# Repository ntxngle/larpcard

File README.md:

# larpcard
what if we larped in larpzhen

It's a NFC that opens apple wallet or payment manager and, when recieving power from NFC communication, blinks the coin's LEDs sequentially.

|Id |Designator                   |Footprint|Quantity                                     |Designation   |Supplier and ref|FIELD7|FIELD8|
|---|-----------------------------|---------|---------------------------------------------|--------------|----------------|------|------|
|1  |D2,D3,D1                     |LED_0603_1608Metric|3                                            |LED           |3x C5278868     |      |      |
|2  |L1                           |1356ant  |1                                            |L             |                |      |      |
|3  |C3,C2,C4                     |C_0603_1608Metric|3                                            |4.7uF         |3x C51933292    |      |      |
|4  |Q2,Q3,Q1                     |SOT-23   |3                                            |NPN           |3x C2936640     |      |      |
|5  |R3,R5,R1                     |R_0603_1608Metric|3                                            |100k          |3x C73806       |      |      |
|6  |R2,R4,R6                     |R_0603_1608Metric|3                                            |100           |3x C2906981     |      |      |
|7  |C6                           |C_0603_1608Metric|1                                            |2pF           |1x C5936367     |      |      |
|8  |C1                           |C_0603_1608Metric|1                                            |220nF         |1x C354388      |      |      |
|9  |U1                           |TSSOP-8_3x3mm_P0.65mm|1                                            |NT3H2111W0FTTJ|1x C7432767     |      |      |
|10 |C5                           |C_0603_1608Metric|1                                            |10uF          |2x C15402       |      |      |
|11 |R8,R7                        |R_0603_1608Metric|2                                            |0             |1x C2654859     |      |      |

Slack username: i10

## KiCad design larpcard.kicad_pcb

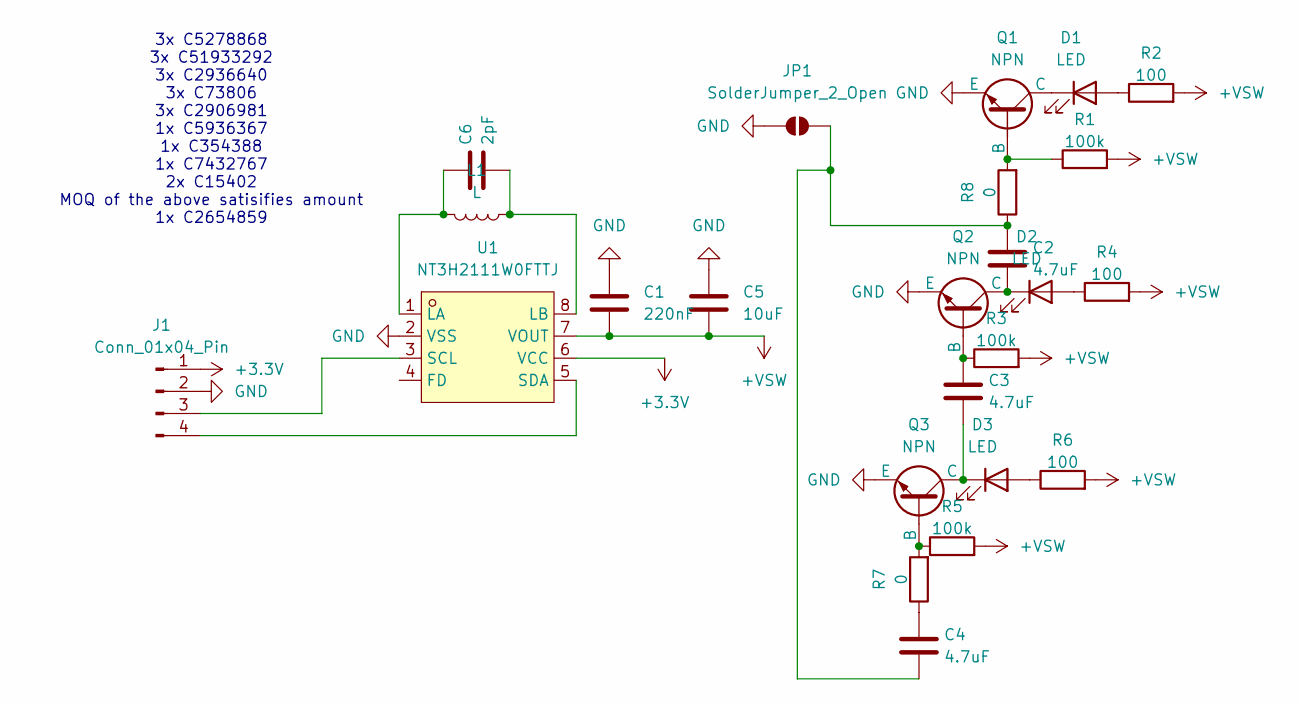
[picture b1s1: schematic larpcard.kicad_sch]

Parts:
C1: 220nF; C_0603_1608Metric
C2, C3, C4: 4.7uF; C_0603_1608Metric
C5: 10uF; C_0603_1608Metric
C6: 2pF; C_0603_1608Metric
D1, D2, D3: LED; LED_0603_1608Metric
J1: Conn_01x04_Pin
JP1: SolderJumper_2_Open; SolderJumper-2_P1.3mm_Open_RoundedPad1.0x1.5mm
L1: L; 1356ant
Q1, Q2, Q3: NPN; SOT-23
R1, R3, R5: 100k; R_0603_1608Metric
R2, R4, R6: 100; R_0603_1608Metric
R7, R8: 0; R_0603_1608Metric
U1: NT3H2111W0FTTJ; TSSOP-8_3x3mm_P0.65mm; MPN NT3H2111W0FTTJ; LCSC Part C2654884

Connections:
+3.3V: J1.1, U1.6 (VCC)
+VSW: C1.2, C5.2, R1.2, R2.2, R3.2, R4.2, R5.2, R6.2, U1.7 (VOUT)
GND: C1.1, C5.1, J1.2, JP1.1 (A), Q1.3 (E), Q2.3 (E), Q3.3 (E), U1.2 (VSS)
unnamed: C4.2, R7.1
unnamed: D1.2 (A), R2.1
unnamed: D1.1 (K), Q1.1 (C)
unnamed: D2.2 (A), R4.1
unnamed: C2.1, D2.1 (K), Q2.1 (C)
unnamed: D3.2 (A), R6.1
unnamed: C3.1, D3.1 (K), Q3.1 (C)
unnamed: J1.3, U1.3 (SCL)
unnamed: J1.4, U1.5 (SDA)
unnamed: C2.2, C4.1, JP1.2 (B), R8.1
unnamed: Q1.2 (B), R1.1, R8.2
unnamed: C3.2, Q2.2 (B), R3.1
unnamed: Q3.2 (B), R5.1, R7.2
unnamed: C6.2, L1.2, U1.1 (LA)
unnamed: C6.1, L1.1, U1.8 (LB)

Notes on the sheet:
3x C5278868 3x C51933292 3x C2936640 3x C73806 3x C2906981 1x C5936367 1x C354388 1x C7432767 2x C15402 MOQ of the above satisifies amount 1x C2654859

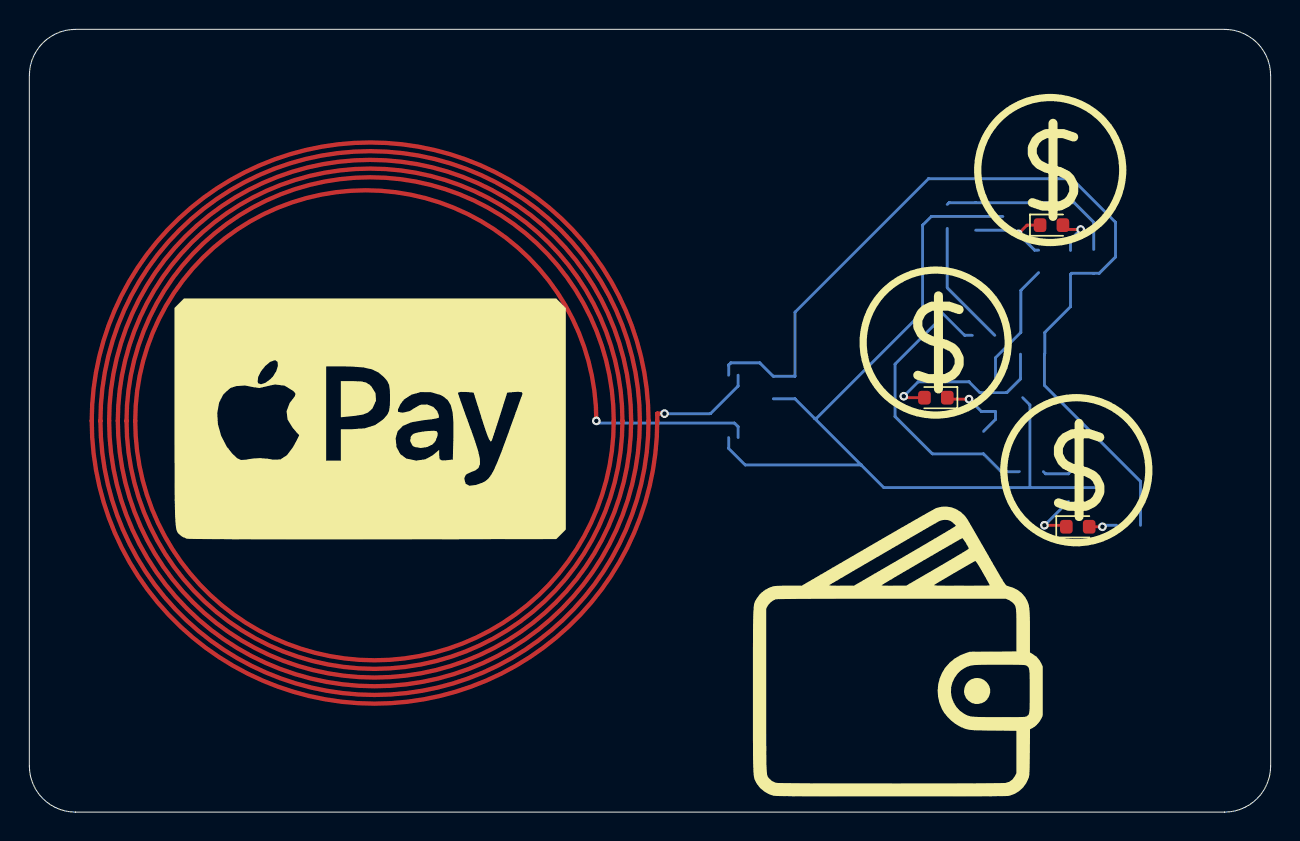
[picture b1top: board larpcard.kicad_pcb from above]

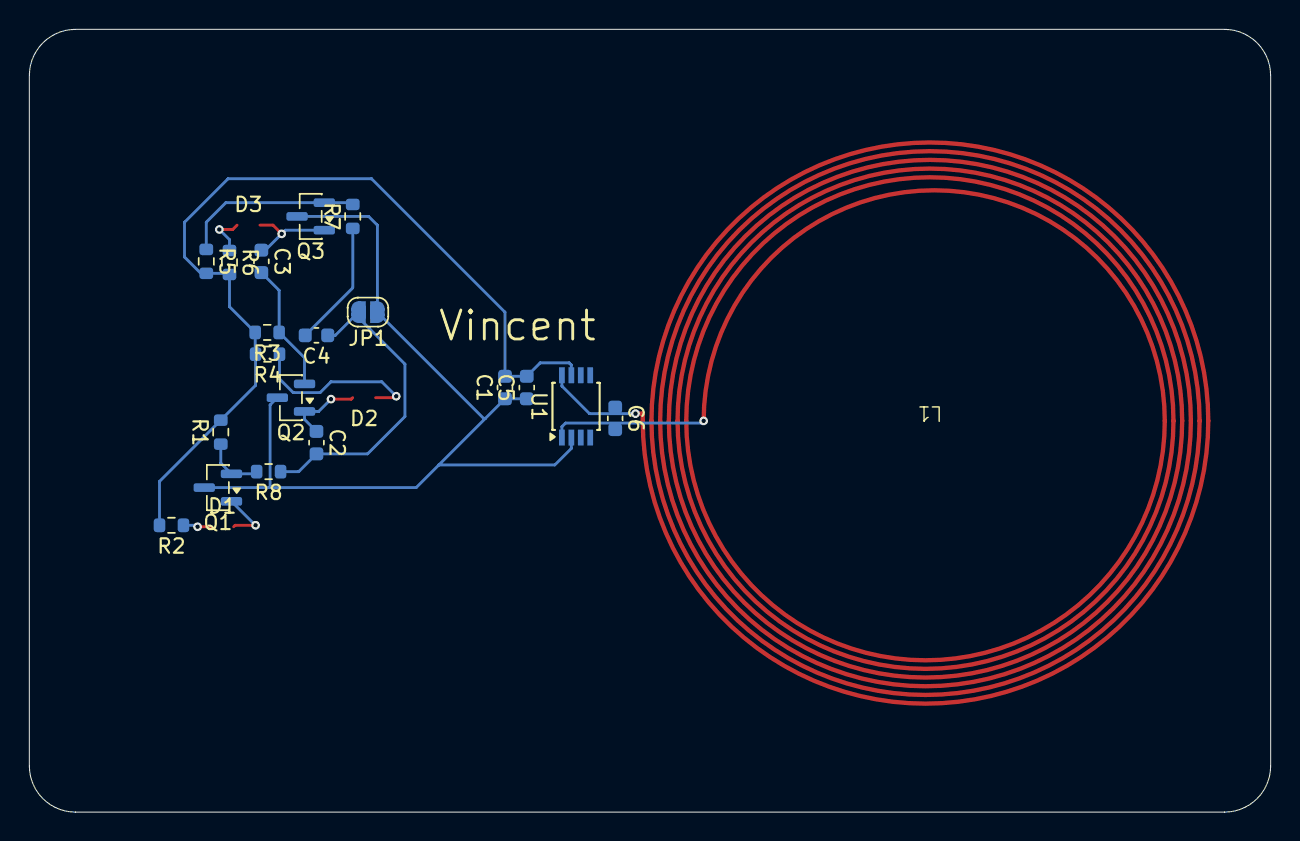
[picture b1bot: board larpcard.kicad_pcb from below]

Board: 2 copper layers, 85.6 x 54.0 mm, 23 parts (19 on the bottom side), 15 nets.
